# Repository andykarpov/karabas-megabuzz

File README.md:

## Karabas-MegaBuzz

English | [Русский](README.ru.md)

Simple FPGA based sound card for ZX Spectrum (NemoBus). 
Inspired by a ZX-Multisound and karabas-opl3 soundcards :)

### Tech specs

* Turbosound FM
* General Sound 2 MB (1.5 MB on Rev.A1 while DivMMC is enabled)
* OPL3 sound by YMF-262-M
* MIDI by Dream SAM2695
* SAA1099
* Soundrive, Covox + Beeper
* MP3, OGG, WMA, AAC decoding by VS1053/VS1063 (Rev.A3)
* MP3 decoding in software on a RISC-V core inside the XC6SLX25, up to 320 kbps stereo
* 16-bit DAC PCM5102
* XC6SLX16 / XC6SLX25 FPGA
* SD Card by Z-Controller / DivMMC (since rev.A1)
* Low profile PCB: 92x44mm
* 5V only power required

### What each board can do

| | Rev.A | Rev.A1 | Rev.A2 | Rev.A3 |
| :--- | :--- | :--- | :--- | :--- |
| TS-FM, GS, OPL3, SAA, Soundrive, Covox, Beeper, MIDI | yes | yes | yes | yes |
| SD card (Z-Controller, DivMMC) | no | yes | yes | yes |
| Settings | DIP switches | DIP switches | configurator | configurator |
| RAM of DivMMC | - | shared with GS | own SRAM | own SRAM |
| MP3 | software, XC6SLX25 only | software, XC6SLX25 only | software, XC6SLX25 only | VS1053 chip; software as an option on XC6SLX25 |

### Getting started

1. Flash the card: see [the manual](HOWTO.en.md) and the [table below](#bitstreams--roms-to-flash-into-the-spi-flash-chip).
2. Prepare the SD card (Rev.A1 and newer):

   ```
   /SYS/               system files of esxDOS 0.8.9
   /BIN/               dot commands of esxDOS
   /BIN/BPLUGINS/mp3   MP3 plugin for the NMI browser, firmware/src/plugin/mp3
   ```

   The esxDOS ROM is built into the bitstream, the SD card needs the matching files from the esxDOS 0.8.9 distribution.
3. Power up the computer, then press RESET or NMI once. The card does not reset the host by itself, and this is what lets DivMMC take over.

### Playing MP3

In the NMI browser by Bob Fossil, with the plugin above, select an MP3 file. It can also play a whole directory. `Space` goes to the next track, `Q` leaves.

The software decoder and the chip work the same for players (registers `#F5`, `#F6`, `#FB`, see [PORTS.en.md](PORTS.en.md)). The software decoder implements the volume only, bass and treble are ignored, and it does not play free format MP3.

Which decoder is used:

* Rev.A, Rev.A1 and Rev.A2 on the XC6SLX25: always the software decoder. These boards have no VS1053 chip.
* Rev.A3 on the XC6SLX25: chosen by the `MP3 on RV32` option of the configurator, the VS1053 chip when it is off.
* Rev.A3 on the XC6SLX16: the VS1053 chip.
* The other boards on the XC6SLX16: no MP3, there is no room for the decoder.

### Settings

#### Rev.A and Rev.A1: DIP switches

A switch left open (or not soldered at all) means the device is enabled.

| Switch | Rev.A | Rev.A1 |
| :--- | :--- | :--- |
| SW1 | Soundrive + Covox + Beeper | DivMMC + Z-Controller |
| SW2 | SAA1099 | Soundrive + Covox + Beeper + SAA1099 |
| SW3 | General Sound | General Sound |
| SW4 | TurboSound FM + MIDI | TurboSound FM + MIDI |
| SW5 | OPL3 | OPL3 |

#### Rev.A2 and Rev.A3: configurator

Hold the RESET and NMI buttons on the card after it has started: the card replaces the ROM of the computer with the configurator.

Use `Q`/`A` or the cursor keys to move, `Space` or `Enter` to change an option or press a button. `APPLY` saves the settings to the flash chip and reboots, `CANCEL` leaves them as they were.

| Option | Meaning |
| :--- | :--- |
| DivMMC | DivMMC with esxDOS |
| ZC | Z-Controller |
| Soundrive | Soundrive and Covox |
| Beeper | Beeper |
| SAA1099 | SAA1099 |
| GS | General Sound |
| TSFM / MIDI | TurboSound FM and MIDI |
| OPL3 | OPL3 |
| VU bar | VU meter as a bar |
| VU dot | VU meter peak dot |
| VU reversed | VU meter in the opposite direction |
| MP3 on RV32 | Rev.A3 on the XC6SLX25: use the software MP3 decoder instead of the VS1053 chip |

The same settings can be changed from a program, see [PORTS.en.md](PORTS.en.md).

### Changelog & current status [ERRATA](ERRATA.en.md)

* Rev.A - initial release

* Rev.A1 - intermediate revision

    * [x] Added SD card
    * [x] Changed OPL3 chip power to 3v3 rail, reset controlled by FPGA
    * [x] Added NMI button
    * [x] Added SD LED
    * [x] Added PSRAM chip
    * [x] Added new signals to grab and emit on nemobus (NMI, ROMCS)
    * [x] Added ability to pass sound out via nemobus slot

* Rev.A2 - current revision

    * [x] Removed DIP switches
    * [x] Added 128kB SRAM chip for DivMMC
    * [x] Added 8kb EEPROM chip to store configuration

* Rev.A3 - current dev version

    * [x] Added VS1053 IC

### How-to & Documentation

Please [read the manual](HOWTO.en.md) how to flash your card with alt tools, like Altera Usb Blaster + openocd.

Some links to the documentation files:

* revA: [Schematics](docs/karabas-megabuzz-revA.pdf), [interactive BOM](docs/karabas-megabuzz-revA-ibom.html)
* revA1: [Schematics](docs/karabas-megabuzz-revA1.pdf), [interactive BOM](docs/karabas-megabuzz-revA1-ibom.html)
* revA2: [Schematics](docs/karabas-megabuzz-revA2.pdf), [interactive BOM](docs/karabas-megabuzz-revA2-ibom.html)
* revA3: [Schematics](docs/karabas-megabuzz-revA3.pdf), [interactive BOM](docs/karabas-megabuzz-revA3-ibom.html)

### Bitstreams & ROMs to flash into the SPI flash chip

| Board Revision | FPGA XC6SLX16 | FPGA XC6SLX25 |
| :--- | :--- | :--- |
| **Rev.A** | • [(Bitstream)](firmware/src/syn/work16/karabas_megabuzz.bin)<br>• [(GS ROM)](firmware/src/rtl/sound/gs105b.rom)<br>• [(CFG)](firmware/src/syn/cfg1.rom) | • [(Bitstream)](firmware/src/syn/work25/karabas_megabuzz.bin)<br>• [(GS ROM)](firmware/src/rtl/sound/gs105b.rom)<br>• [(CFG)](firmware/src/syn/cfg1.rom)<br>• [(MP3 firmware)](firmware/src/syn/mp3dec.bin) |
| **Rev.A1** | • [(Bitstream)](firmware/src/syn/work16/karabas_megabuzz_a1.bin)<br>• [(GS ROM)](firmware/src/rtl/sound/gs105b.rom)<br>• [(CFG)](firmware/src/syn/cfg1.rom) | • [(Bitstream)](firmware/src/syn/work25/karabas_megabuzz_a1.bin)<br>• [(GS ROM)](firmware/src/rtl/sound/gs105b.rom)<br>• [(CFG)](firmware/src/syn/cfg1.rom)<br>• [(MP3 firmware)](firmware/src/syn/mp3dec.bin) |
| **Rev.A2** | • [(Bitstream)](firmware/src/syn/work16/karabas_megabuzz_a2.bin)<br>• [(GS ROM)](firmware/src/rtl/sound/gs105b.rom)<br>• [(CFG)](firmware/src/syn/cfg1.rom) | • [(Bitstream)](firmware/src/syn/work25/karabas_megabuzz_a2.bin)<br>• [(GS ROM)](firmware/src/rtl/sound/gs105b.rom)<br>• [(CFG)](firmware/src/syn/cfg1_a2_rv32.rom)<br>• [(MP3 firmware)](firmware/src/syn/mp3dec.bin) |
| **Rev.A3** | • [(Bitstream)](firmware/src/syn/work16/karabas_megabuzz_a3.bin)<br>• [(GS ROM)](firmware/src/rtl/sound/gs105b.rom)<br>• [(CFG)](firmware/src/syn/cfg1.rom) | • [(Bitstream)](firmware/src/syn/work25/karabas_megabuzz_a3.bin)<br>• [(GS ROM)](firmware/src/rtl/sound/gs105b.rom)<br>• [(CFG)](firmware/src/syn/cfg1.rom)<br>• [(MP3 firmware)](firmware/src/syn/mp3dec.bin) |

Flash layout: bitstream at `0x000000`, GS ROM at `0x100000`, MP3 firmware at `0x180000` (XC6SLX25 only), configuration at `0x1F0000`.

### Related projects

* Karabas-OPL3 - [link](https://github.com/andykarpov/karabas-opl3)
* BomgeMoon - [link](https://github.com/Kulicheg/BomgeMoon)
* ZX-Multisound - [link](https://github.com/UzixLS/zx-multisound)
* Turbo Sound FM - [link](http://www.nedopc.com/TURBOSOUND/ts-fm.php)
* ZXM-SoundCard - [link](http://micklab.ru/My%20Soundcard/ZXMSoundCard.htm)
* ZXM-GeneralSound - [link](http://micklab.ru/My%20Soundcard/ZXMGeneralSound.htm)
* NeoGS - [link](http://www.nedopc.com/gs/ngs.php)

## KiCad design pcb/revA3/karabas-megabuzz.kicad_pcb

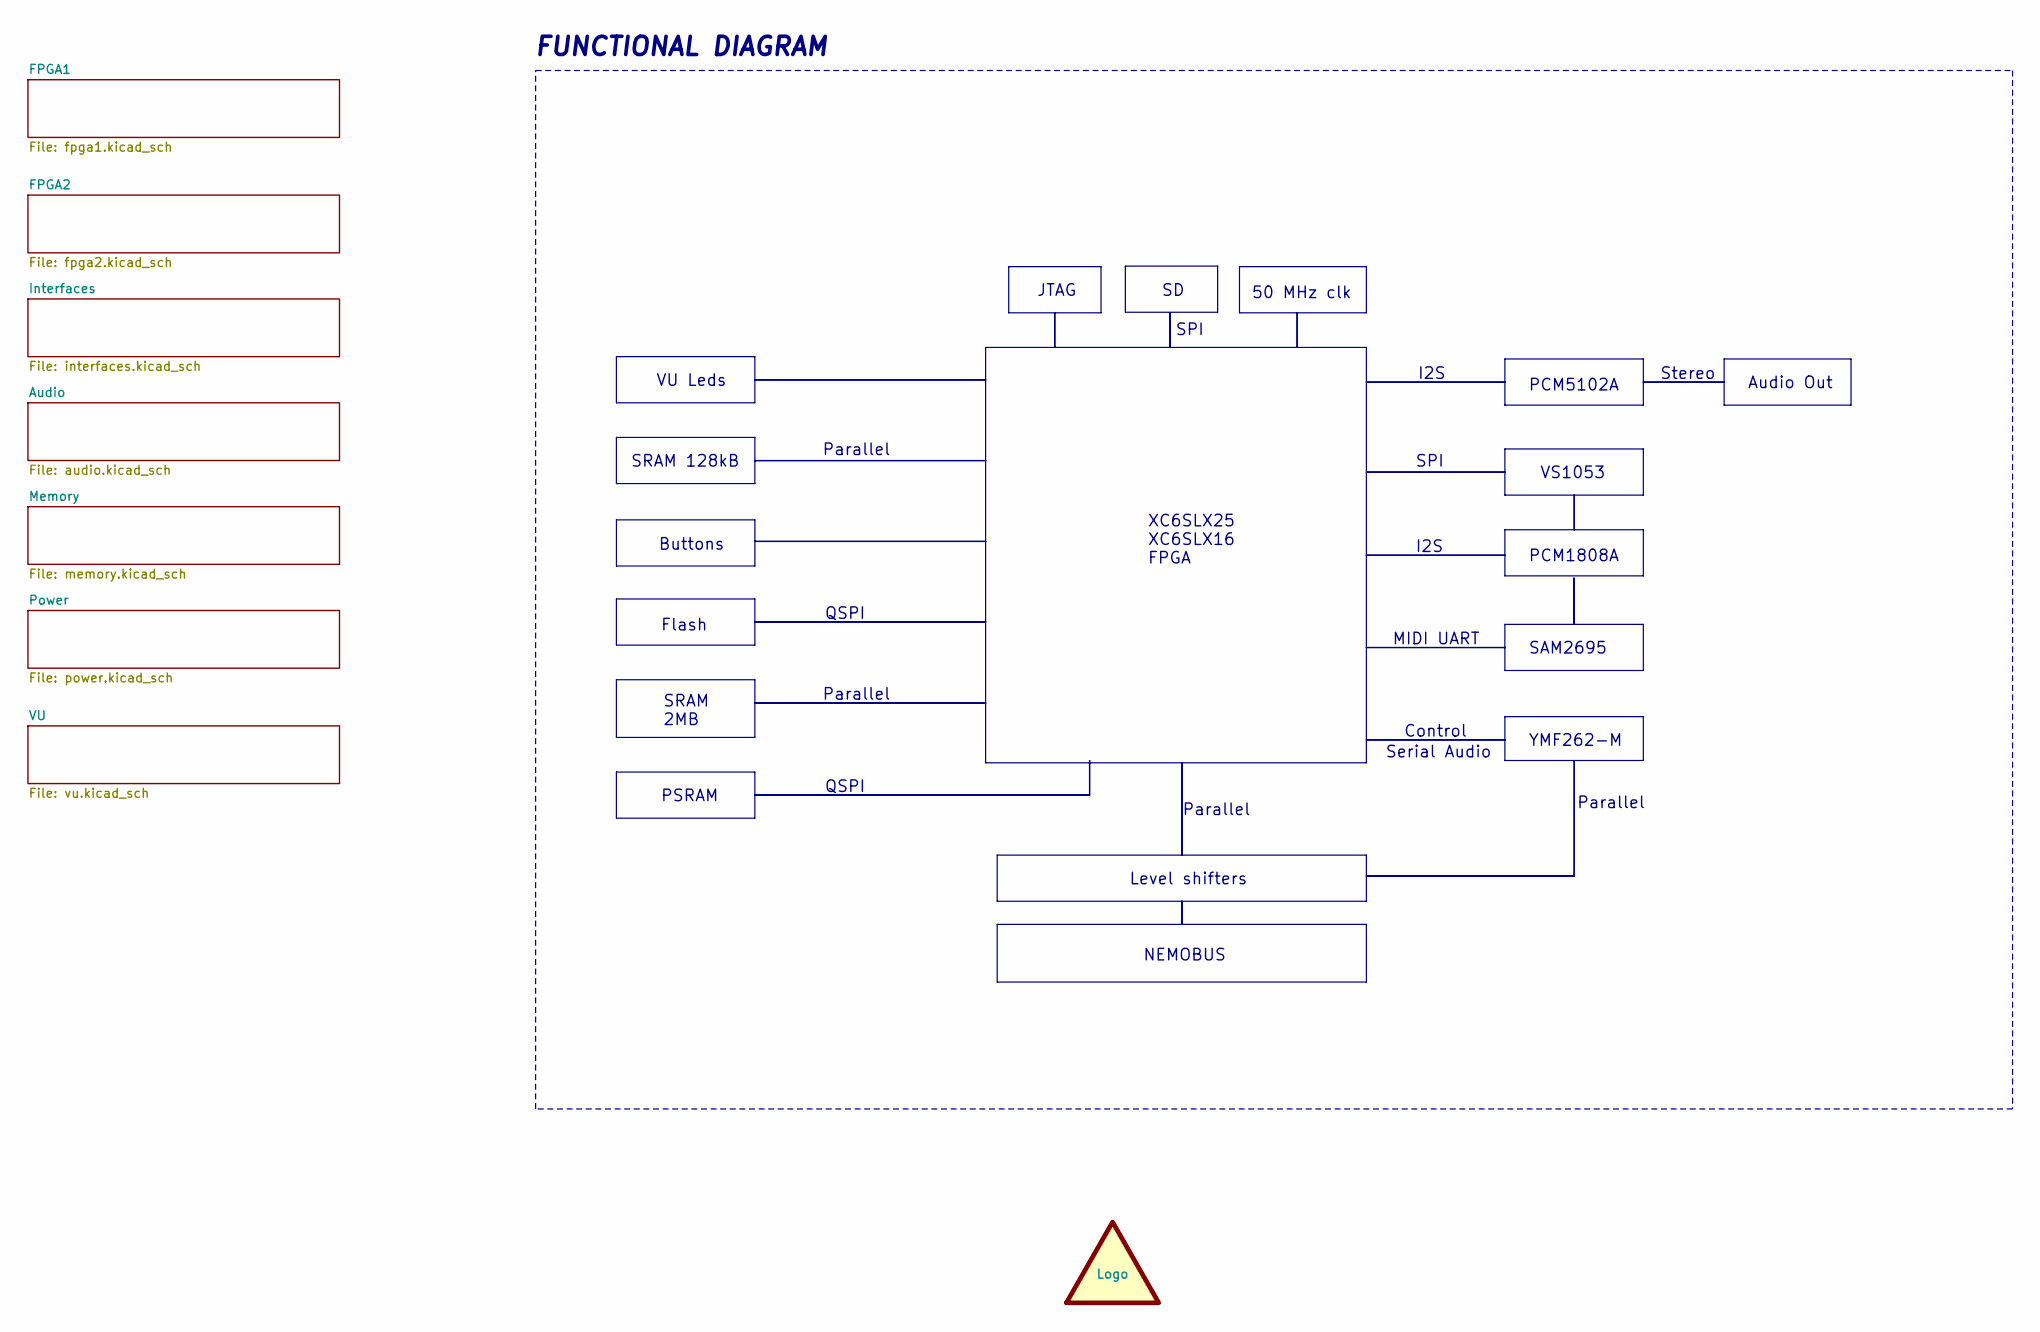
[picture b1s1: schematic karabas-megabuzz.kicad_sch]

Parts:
LOGO1: graphic; andy_karpov_logo5_silk

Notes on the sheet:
PCM5102A
VU Leds
XC6SLX25 XC6SLX16 FPGA
MIDI UART
Buttons
PCM1808A
VS1053
Parallel
YMF262-M
NEMOBUS
SRAM 128kB
Audio Out
I2S
QSPI
SPI
JTAG
50 MHz clk
Flash
SRAM 2MB
Level shifters
Control
Serial Audio
PSRAM
FUNCTIONAL DIAGRAM
SAM2695
Stereo

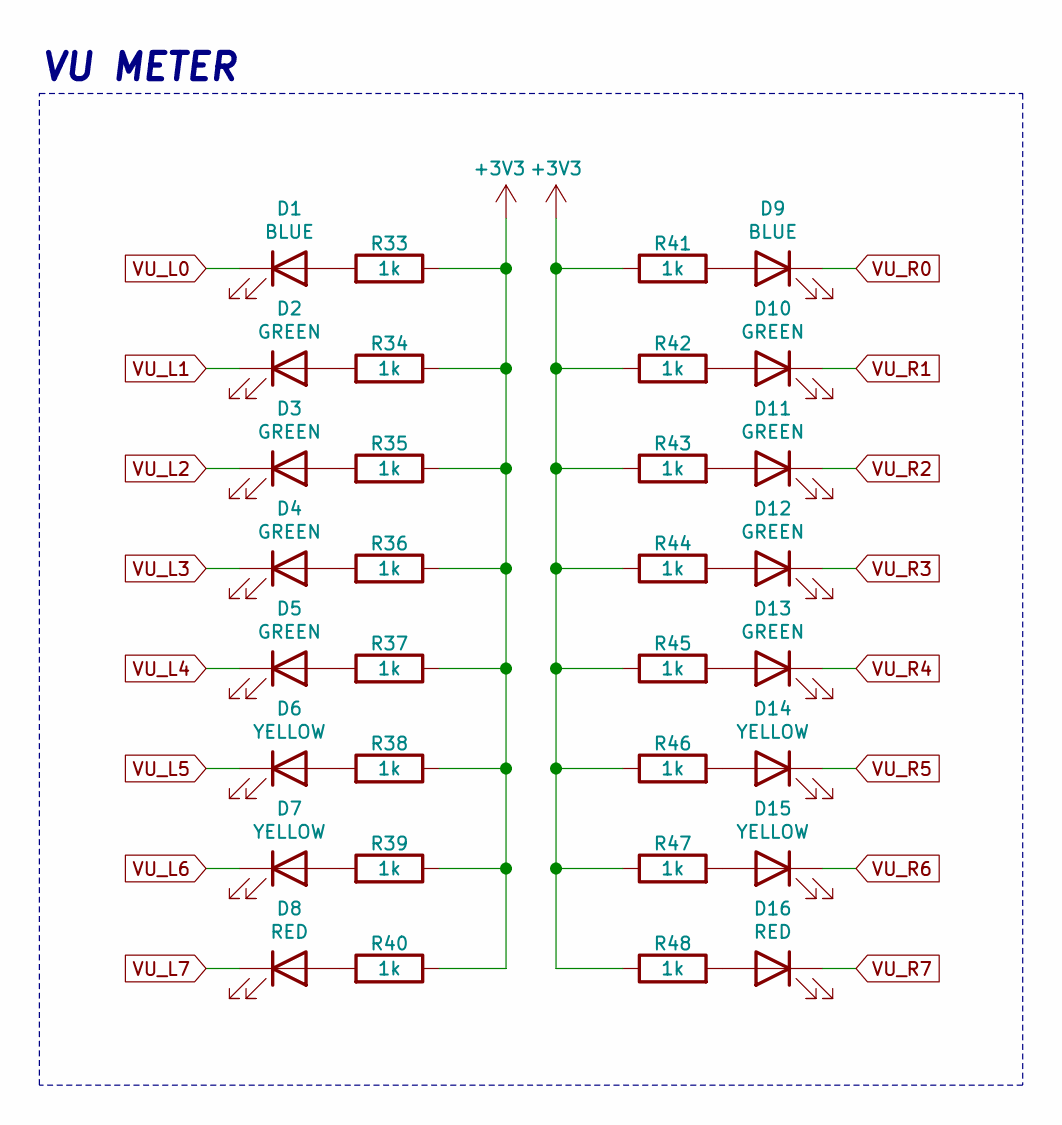
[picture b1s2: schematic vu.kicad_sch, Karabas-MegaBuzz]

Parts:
D1, D9: BLUE; LED_0603_1608Metric_Pad1.05x0.95mm_HandSolder
D2, D3, D4, D5, D10, D11, D12, D13: GREEN; LED_0603_1608Metric_Pad1.05x0.95mm_HandSolder
D6, D7, D14, D15: YELLOW; LED_0603_1608Metric_Pad1.05x0.95mm_HandSolder
D8, D16: RED; LED_0603_1608Metric_Pad1.05x0.95mm_HandSolder
R33, R34, R35, R36, R37, R38, R39, R40, R41, R42, R43, R44, R45, R46, R47, R48: 1k; R_0603_1608Metric_Pad0.98x0.95mm_HandSolder

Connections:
+3V3: R33.1, R34.1, R35.1, R36.1, R37.1, R38.1, R39.1, R40.1, R41.1, R42.1, R43.1, R44.1, R45.1, R46.1, R47.1, R48.1; also elsewhere on the board
unnamed: D1.2 (A), R33.2
unnamed: D2.2 (A), R34.2
unnamed: D3.2 (A), R35.2
unnamed: D4.2 (A), R36.2
unnamed: D5.2 (A), R37.2
unnamed: D6.2 (A), R38.2
unnamed: D7.2 (A), R39.2
unnamed: D8.2 (A), R40.2
unnamed: D9.2 (A), R41.2
unnamed: D10.2 (A), R42.2
unnamed: D11.2 (A), R43.2
unnamed: D12.2 (A), R44.2
unnamed: D13.2 (A), R45.2
unnamed: D14.2 (A), R46.2
unnamed: D15.2 (A), R47.2
unnamed: D16.2 (A), R48.2
VU_L0: D1.1 (K); also elsewhere on the board
VU_L1: D2.1 (K); also elsewhere on the board
VU_L2: D3.1 (K); also elsewhere on the board
VU_L3: D4.1 (K); also elsewhere on the board
VU_L4: D5.1 (K); also elsewhere on the board
VU_L5: D6.1 (K); also elsewhere on the board
VU_L6: D7.1 (K); also elsewhere on the board
VU_L7: D8.1 (K); also elsewhere on the board
VU_R0: D9.1 (K); also elsewhere on the board
VU_R1: D10.1 (K); also elsewhere on the board
VU_R2: D11.1 (K); also elsewhere on the board
VU_R3: D12.1 (K); also elsewhere on the board
VU_R4: D13.1 (K); also elsewhere on the board
VU_R5: D14.1 (K); also elsewhere on the board
VU_R6: D15.1 (K); also elsewhere on the board
VU_R7: D16.1 (K); also elsewhere on the board

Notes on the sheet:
VU METER

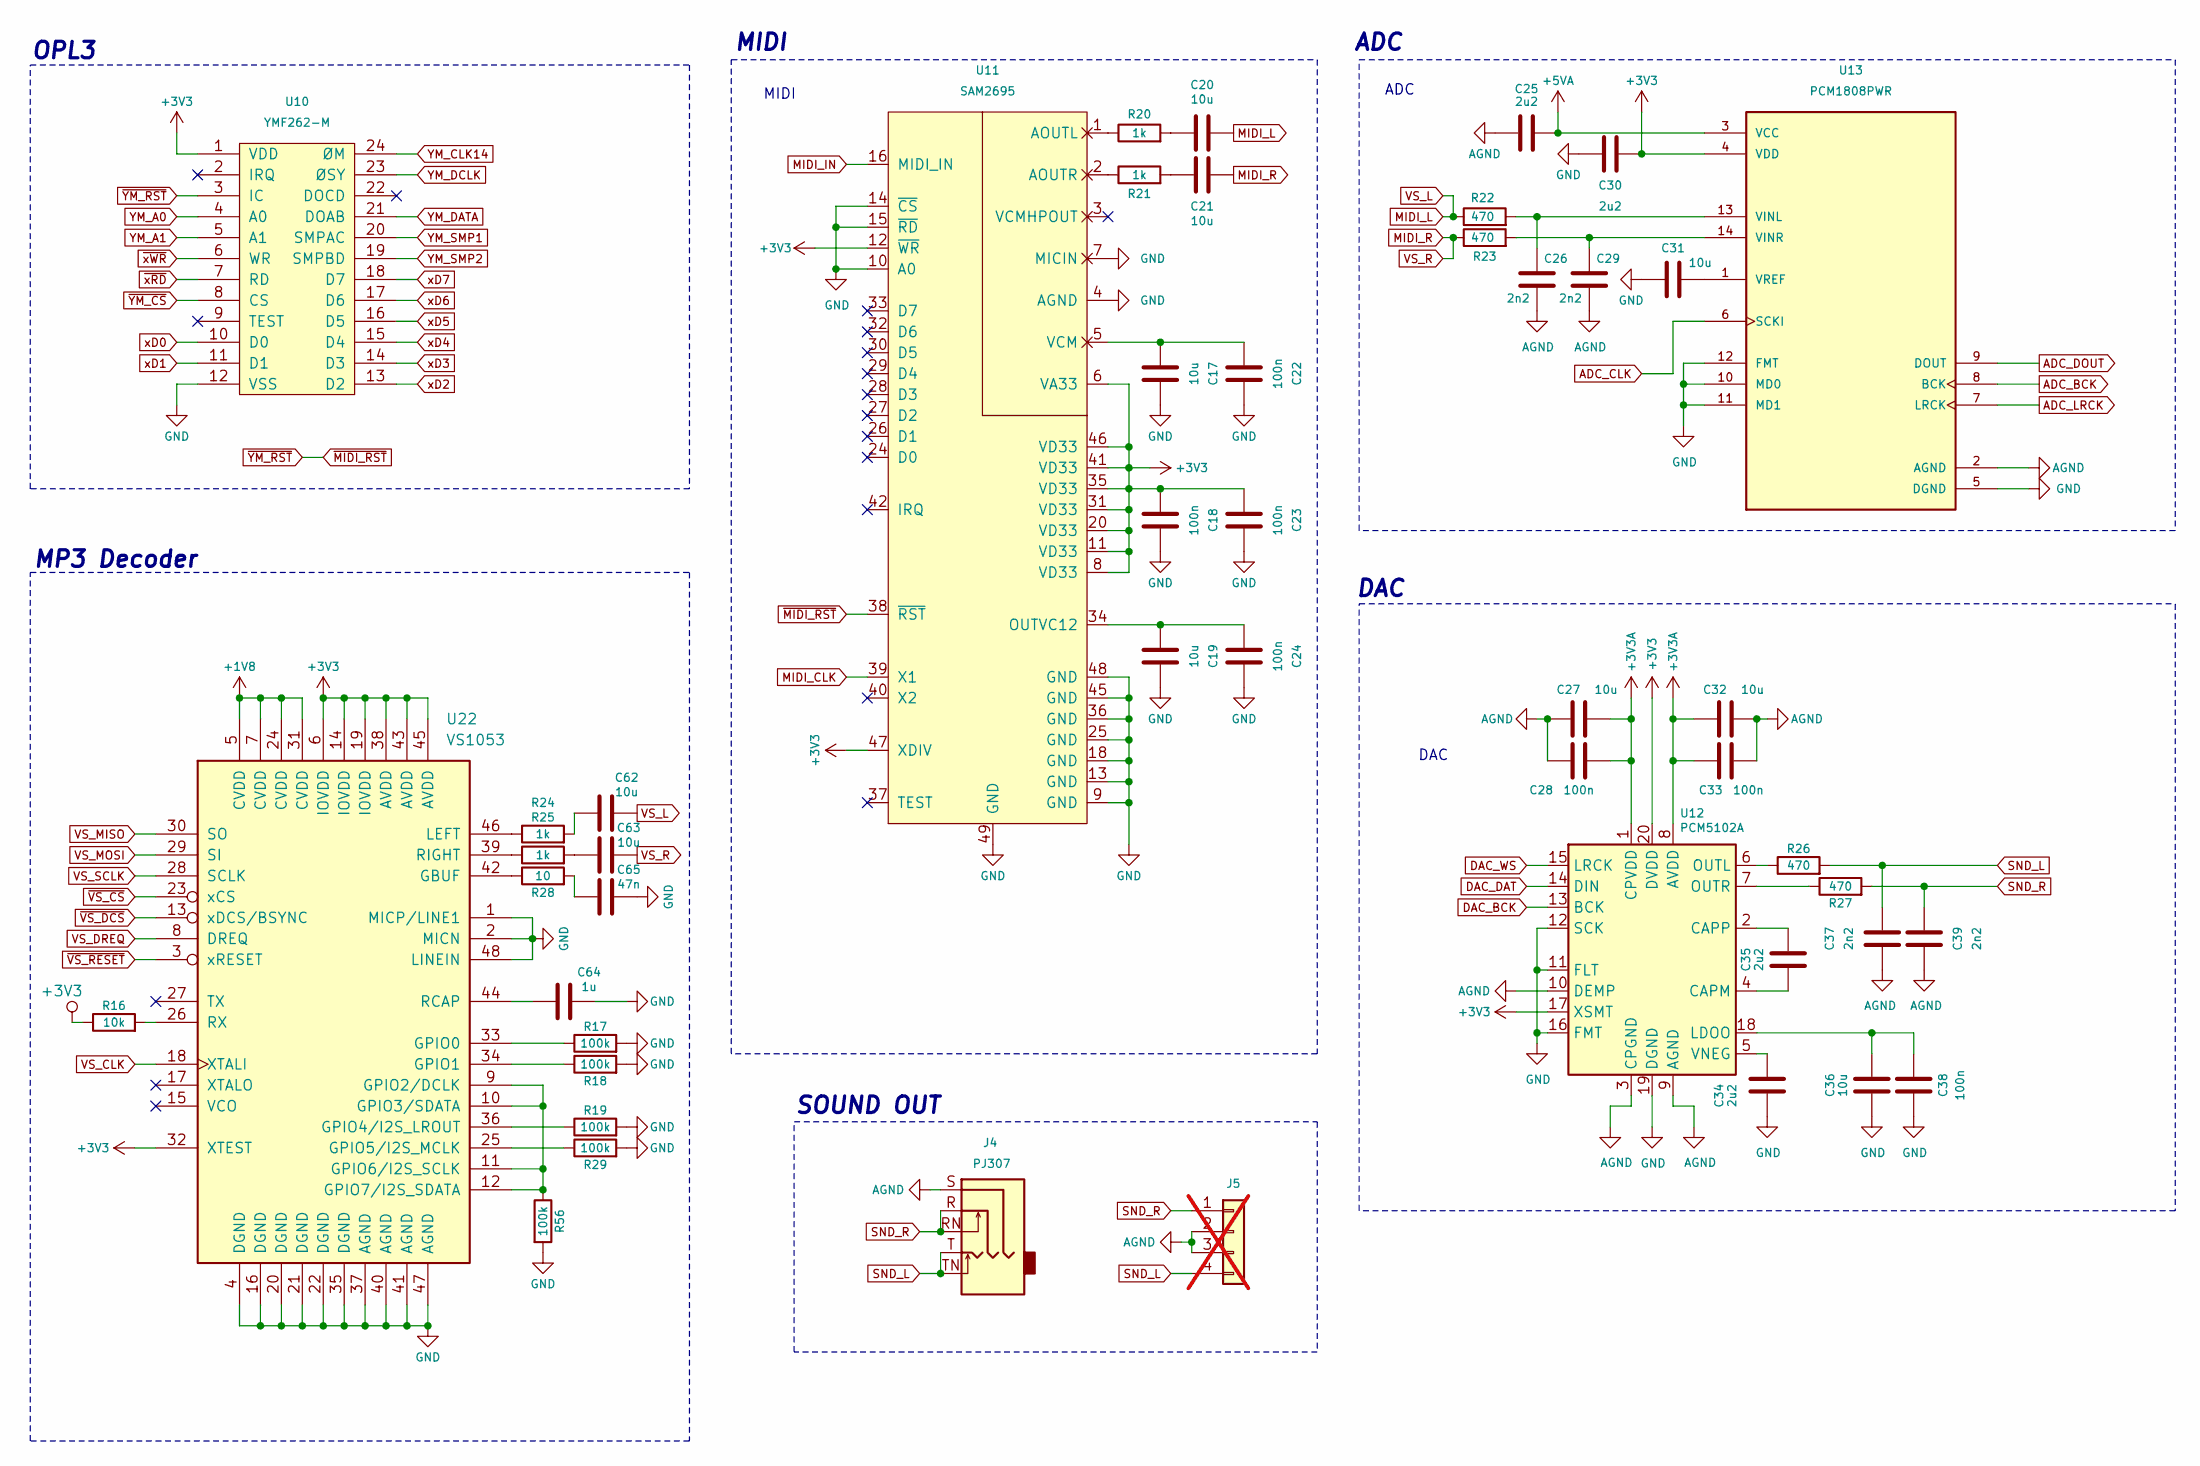
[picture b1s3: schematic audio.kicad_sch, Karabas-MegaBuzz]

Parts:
C17, C19, C20, C21, C27, C31, C32, C36, C62, C63: 10u; C_0603_1608Metric_Pad1.08x0.95mm_HandSolder
C18, C22, C23, C24, C28, C33, C38: 100n; C_0603_1608Metric_Pad1.08x0.95mm_HandSolder
C25, C30, C34, C35: 2u2; C_0603_1608Metric_Pad1.08x0.95mm_HandSolder
C26, C29, C37, C39: 2n2; C_0603_1608Metric_Pad1.08x0.95mm_HandSolder
C64: 1u; C_0603_1608Metric_Pad1.08x0.95mm_HandSolder
C65: 47n; C_0603_1608Metric_Pad1.08x0.95mm_HandSolder
J4: PJ307; Jack_3.5mm_CUI_SJ1-3525N_Horizontal
J5: Conn_01x04; PinHeader_1x04_P2.54mm_Vertical; not fitted
R16: 10k; R_0603_1608Metric_Pad0.98x0.95mm_HandSolder
R17, R18, R19, R29, R56: 100k; R_0603_1608Metric_Pad0.98x0.95mm_HandSolder
R20, R21, R24, R25: 1k; R_0603_1608Metric_Pad0.98x0.95mm_HandSolder
R22, R23, R26, R27: 470; R_0603_1608Metric_Pad0.98x0.95mm_HandSolder
R28: 10; R_0603_1608Metric_Pad0.98x0.95mm_HandSolder
U10: YMF262-M; ymf-262-m
U11: SAM2695; QFN-48-1EP_6x6mm_P0.4mm_EP4.2x4.2mm
U12: PCM5102A; TSSOP-20_4.4x6.5mm_P0.65mm
U13: PCM1808PWR; TSSOP-14_4.4x5mm_P0.65mm; PARTREV B
U22: VS1053; LQFP-48_7x7mm_P0.5mm

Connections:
+1V8: U22.5 (CVDD), U22.7 (CVDD), U22.24 (CVDD), U22.31 (CVDD); also elsewhere on the board
+3V3: C18.1, C23.1, C30.1, R16.1, U10.1 (VDD), U11.6 (VA33), U11.8 (VD33), U11.11 (VD33), U11.12 (~WR), U11.20 (VD33), U11.31 (VD33), U11.35 (VD33), U11.41 (VD33), U11.46 (VD33), U11.47 (XDIV), U12.17 (XSMT), U12.20 (DVDD), U13.4 (VDD), U22.6 (IOVDD), U22.14 (IOVDD), U22.19 (IOVDD), U22.32 (XTEST), U22.38 (AVDD), U22.43 (AVDD), U22.45 (AVDD); also elsewhere on the board
+3V3A: C27.1, C28.1, C32.2, C33.2, U12.1 (CPVDD), U12.8 (AVDD); also elsewhere on the board
+5VA: C25.2, U13.3 (VCC); also elsewhere on the board
ADC_BCK: U13.8 (BCK); also elsewhere on the board
ADC_CLK: U13.6 (SCKI); also elsewhere on the board
ADC_DOUT: U13.9 (DOUT); also elsewhere on the board
ADC_LRCK: U13.7 (LRCK); also elsewhere on the board
AGND: C25.1, C26.2, C27.2, C28.2, C29.2, C32.1, C33.1, C37.1, C39.1, J4.S, J5.2, J5.3, U12.3 (CPGND), U12.9 (AGND), U12.10 (DEMP), U13.2 (AGND); also elsewhere on the board
DAC_BCK: U12.13 (BCK); also elsewhere on the board
DAC_DAT: U12.14 (DIN); also elsewhere on the board
DAC_WS: U12.15 (LRCK); also elsewhere on the board
GND: C17.2, C18.2, C19.2, C22.2, C23.2, C24.2, C30.2, C31.1, C34.1, C36.1, C38.1, C64.2, C65.2, R17.2, R18.2, R19.2, R29.2, R56.2, U10.12 (VSS), U11.4 (AGND), U11.7 (MICIN), U11.9 (GND), U11.10 (A0), U11.13 (GND), U11.14 (~CS), U11.15 (~RD), U11.18 (GND), U11.25 (GND), U11.36 (GND), U11.45 (GND), U11.48 (GND), U11.49 (GND), U12.11 (FLT), U12.12 (SCK), U12.16 (FMT), U12.19 (DGND), U13.5 (DGND), U13.10 (MD0), U13.11 (MD1), U13.12 (FMT), U22.1 (MICP/LINE1), U22.2 (MICN), U22.4 (DGND), U22.16 (DGND), U22.20 (DGND), U22.21 (DGND), U22.22 (DGND), U22.35 (DGND), U22.37 (AGND), U22.40 (AGND), U22.41 (AGND), U22.47 (AGND), U22.48 (LINEIN); also elsewhere on the board
MIDI_CLK: U11.39 (X1); also elsewhere on the board
MIDI_IN: U11.16 (MIDI_IN); also elsewhere on the board
MIDI_L: C20.2, C62.2, R22.1
MIDI_R: C21.2, C63.2, R23.1
unnamed: C20.1, R20.2
unnamed: C21.1, R21.2
unnamed: C62.1, R24.2
unnamed: C63.1, R25.2
unnamed: C65.1, R28.2
unnamed: R20.1, U11.1 (AOUTL)
unnamed: R21.1, U11.2 (AOUTR)
unnamed: C19.1, C24.1, U11.34 (OUTVC12)
unnamed: C17.1, C22.1, U11.5 (VCM)
unnamed: C35.1, U12.4 (CAPM)
unnamed: C35.2, U12.2 (CAPP)
unnamed: C36.2, C38.2, U12.18 (LDOO)
unnamed: R26.1, U12.6 (OUTL)
unnamed: R27.1, U12.7 (OUTR)
unnamed: C34.2, U12.5 (VNEG)
unnamed: C26.1, R22.2, U13.13 (VINL)
unnamed: C29.1, R23.2, U13.14 (VINR)
unnamed: C31.2, U13.1 (VREF)
unnamed: R28.1, U22.42 (GBUF)
unnamed: R17.1, U22.33 (GPIO0)
unnamed: R18.1, U22.34 (GPIO1)
unnamed: R56.1, U22.9 (GPIO2/DCLK), U22.10 (GPIO3/SDATA), U22.11 (GPIO6/I2S_SCLK), U22.12 (GPIO7/I2S_SDATA)
unnamed: R19.1, U22.36 (GPIO4/I2S_LROUT)
unnamed: R29.1, U22.25 (GPIO5/I2S_MCLK)
unnamed: R24.1, U22.46 (LEFT)
unnamed: C64.1, U22.44 (RCAP)
unnamed: R25.1, U22.39 (RIGHT)
unnamed: R16.2, U22.26 (RX)
SND_L: C37.2, J4.T, J4.TN, J5.4, R26.2; also elsewhere on the board
SND_R: C39.2, J4.R, J4.RN, J5.1, R27.2; also elsewhere on the board
VS_CLK: U22.18 (XTALI); also elsewhere on the board
VS_DREQ: U22.8 (DREQ); also elsewhere on the board
VS_MISO: U22.30 (SO); also elsewhere on the board
VS_MOSI: U22.29 (SI); also elsewhere on the board
VS_SCLK: U22.28 (SCLK); also elsewhere on the board
YM_A0: U10.4 (A0); also elsewhere on the board
YM_A1: U10.5 (A1); also elsewhere on the board
YM_CLK14: U10.24 (ØM); also elsewhere on the board
YM_DATA: U10.21 (DOAB); also elsewhere on the board
YM_DCLK: U10.23 (ØSY); also elsewhere on the board
YM_SMP1: U10.20 (SMPAC); also elsewhere on the board
YM_SMP2: U10.19 (SMPBD); also elsewhere on the board
xD0: U10.10 (D0); also elsewhere on the board
xD1: U10.11 (D1); also elsewhere on the board
xD2: U10.13 (D2); also elsewhere on the board
xD3: U10.14 (D3); also elsewhere on the board
xD4: U10.15 (D4); also elsewhere on the board
xD5: U10.16 (D5); also elsewhere on the board
xD6: U10.17 (D6); also elsewhere on the board
xD7: U10.18 (D7); also elsewhere on the board
~MIDI_RST: U10.3 (IC), U11.38 (~RST); also elsewhere on the board
~VS_CS: U22.23 (xCS); also elsewhere on the board
~VS_DCS: U22.13 (xDCS/BSYNC); also elsewhere on the board
~VS_RESET: U22.3 (xRESET); also elsewhere on the board
~YM_CS: U10.8 (CS); also elsewhere on the board
~xRD: U10.7 (RD); also elsewhere on the board
~xWR: U10.6 (WR); also elsewhere on the board

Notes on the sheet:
SOUND OUT
MP3 Decoder
ADC
MIDI
DAC
OPL3

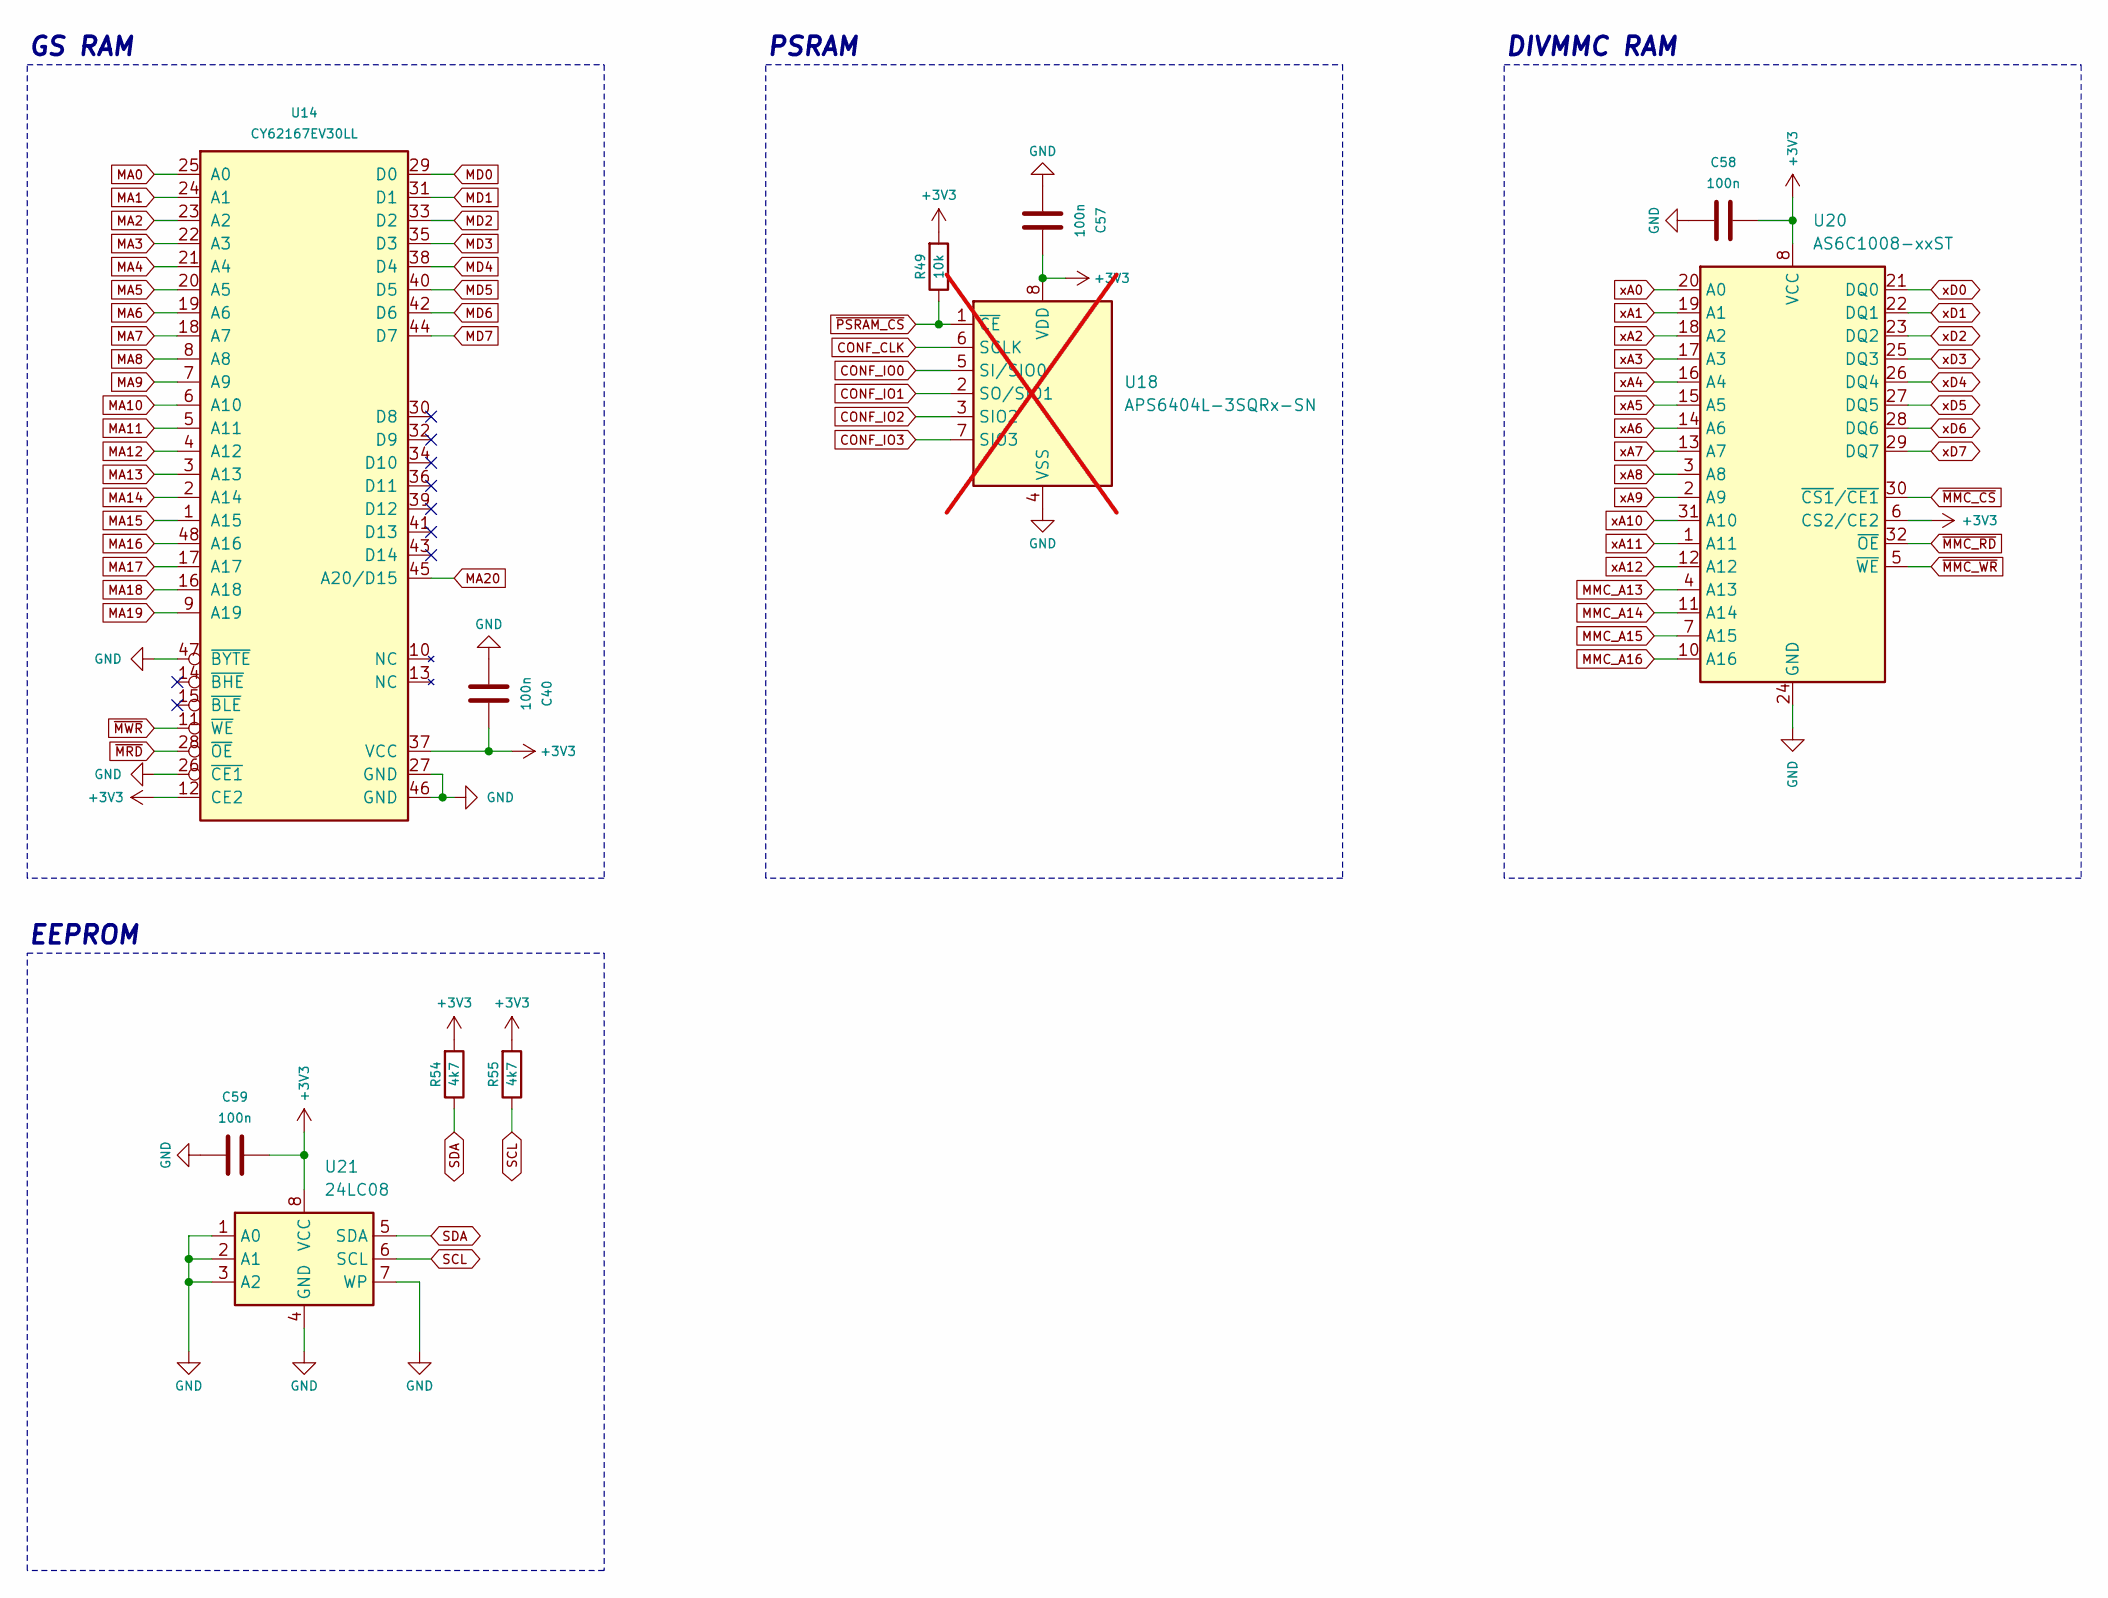
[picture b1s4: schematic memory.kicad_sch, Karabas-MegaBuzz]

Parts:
C40, C57, C58, C59: 100n; C_0603_1608Metric_Pad1.08x0.95mm_HandSolder
R49: 10k; R_0603_1608Metric_Pad0.98x0.95mm_HandSolder
R54, R55: 4k7; R_0603_1608Metric_Pad0.98x0.95mm_HandSolder
U14: CY62167EV30LL; TSOP-I-48_18.4x12mm_P0.5mm
U18: APS6404L-3SQRx-SN; SOIC-8_3.9x4.9mm_P1.27mm; not fitted
U20: AS6C1008-xxST; TSOP-I-32_11.8x8mm_P0.5mm
U21: 24LC08; SOIC-8_3.9x4.9mm_P1.27mm

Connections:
+3V3: C40.2, C57.2, C58.2, C59.2, R49.2, R54.2, R55.2, U14.12 (CE2), U14.37 (VCC), U18.8 (VDD), U20.6 (CS2/CE2), U20.8 (VCC), U21.8 (VCC); also elsewhere on the board
CONF_CLK: U18.6 (SCLK); also elsewhere on the board
CONF_IO0: U18.5 (SI/SIO0); also elsewhere on the board
CONF_IO1: U18.2 (SO/SIO1); also elsewhere on the board
CONF_IO2: U18.3 (SIO2); also elsewhere on the board
CONF_IO3: U18.7 (SIO3); also elsewhere on the board
GND: C40.1, C57.1, C58.1, C59.1, U14.26 (~CE1), U14.27 (GND), U14.46 (GND), U14.47 (~BYTE), U18.4 (VSS), U20.24 (GND), U21.1 (A0), U21.2 (A1), U21.3 (A2), U21.4 (GND), U21.7 (WP); also elsewhere on the board
MA0: U14.25 (A0); also elsewhere on the board
MA1: U14.24 (A1); also elsewhere on the board
MA2: U14.23 (A2); also elsewhere on the board
MA3: U14.22 (A3); also elsewhere on the board
MA4: U14.21 (A4); also elsewhere on the board
MA5: U14.20 (A5); also elsewhere on the board
MA6: U14.19 (A6); also elsewhere on the board
MA7: U14.18 (A7); also elsewhere on the board
MA8: U14.8 (A8); also elsewhere on the board
MA9: U14.7 (A9); also elsewhere on the board
MA10: U14.6 (A10); also elsewhere on the board
MA11: U14.5 (A11); also elsewhere on the board
MA12: U14.4 (A12); also elsewhere on the board
MA13: U14.3 (A13); also elsewhere on the board
MA14: U14.2 (A14); also elsewhere on the board
MA15: U14.1 (A15); also elsewhere on the board
MA16: U14.48 (A16); also elsewhere on the board
MA17: U14.17 (A17); also elsewhere on the board
MA18: U14.16 (A18); also elsewhere on the board
MA19: U14.9 (A19); also elsewhere on the board
MA20: U14.45 (A20/D15); also elsewhere on the board
MD0: U14.29 (D0); also elsewhere on the board
MD1: U14.31 (D1); also elsewhere on the board
MD2: U14.33 (D2); also elsewhere on the board
MD3: U14.35 (D3); also elsewhere on the board
MD4: U14.38 (D4); also elsewhere on the board
MD5: U14.40 (D5); also elsewhere on the board
MD6: U14.42 (D6); also elsewhere on the board
MD7: U14.44 (D7); also elsewhere on the board
MMC_A13: U20.4 (A13); also elsewhere on the board
MMC_A14: U20.11 (A14); also elsewhere on the board
MMC_A15: U20.7 (A15); also elsewhere on the board
MMC_A16: U20.10 (A16); also elsewhere on the board
SCL: R55.1, U21.6 (SCL); also elsewhere on the board
SDA: R54.1, U21.5 (SDA); also elsewhere on the board
xA0: U20.20 (A0); also elsewhere on the board
xA1: U20.19 (A1); also elsewhere on the board
xA2: U20.18 (A2); also elsewhere on the board
xA3: U20.17 (A3); also elsewhere on the board
xA4: U20.16 (A4); also elsewhere on the board
xA5: U20.15 (A5); also elsewhere on the board
xA6: U20.14 (A6); also elsewhere on the board
xA7: U20.13 (A7); also elsewhere on the board
xA8: U20.3 (A8); also elsewhere on the board
xA9: U20.2 (A9); also elsewhere on the board
xA10: U20.31 (A10); also elsewhere on the board
xA11: U20.1 (A11); also elsewhere on the board
xA12: U20.12 (A12); also elsewhere on the board
xD0: U20.21 (DQ0); also elsewhere on the board
xD1: U20.22 (DQ1); also elsewhere on the board
xD2: U20.23 (DQ2); also elsewhere on the board
xD3: U20.25 (DQ3); also elsewhere on the board
xD4: U20.26 (DQ4); also elsewhere on the board
xD5: U20.27 (DQ5); also elsewhere on the board
xD6: U20.28 (DQ6); also elsewhere on the board
xD7: U20.29 (DQ7); also elsewhere on the board
~MMC_CS: U20.30 (~CS1/~CE1); also elsewhere on the board
~MMC_RD: U20.32 (~OE); also elsewhere on the board
~MMC_WR: U20.5 (~WE); also elsewhere on the board
~MRD: U14.28 (~OE); also elsewhere on the board
~MWR: U14.11 (~WE); also elsewhere on the board
~PSRAM_CS: R49.1, U18.1 (~CE); also elsewhere on the board

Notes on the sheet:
PSRAM
GS RAM
DIVMMC RAM
EEPROM
